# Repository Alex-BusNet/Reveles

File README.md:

**Reveles** (<i>verb</i>) - Latin; to discover or detect.

<ul style="list-style-type: none">
	<li><a href="#about">About</a></li>
	<li><a href="#tools-needed">Tools needed</a></li>
	<li><a href="#setup">Setup</a>
		<ul>
			<li><a href="#installing-linux">Installing Linux</a></li>
			<li><a href="#installing-git">Installing Git</a></li>
			<li><a href="#setting-up-your-working-directories">Setting Up Your Working Directories</a></li>
			<li><a href="#installing-qt-host-pc">Installing Qt</a></li>
			<li><a href="#building-and-configuring-opencv">Building and Configuring OpenCV</a>
				<ul>
					<li><a href="#setup">Setup</a></li>
					<li><a href="#build">Build</a></li>
				</ul>
			</li>
			<li><a href="#installing-wiringpi">Installing WiringPi</a></li>
			<li><a href="#installing-raspicam">Installing Raspicam</a></li>
			<li><a href="#setting-up-the-cross-compiler-tools">Setting Up the Cross Compiler Tools</a></li>
		</ul>
	</li>
	<li><a href="#building-reveles">Building Reveles</a>
		<ul>
			<li><a href="#obtaining-reveles">Obtaining Reveles</a></li>
			<li><a href="#bringing-it-all-together">Bringing it all Together</a></li>
		</ul>
	</li>
	<li><a href="#troubleshooting">Troubleshooting</a>
		<ul>
			<li><a href="#eglfs-not-found">EGLFS not found</a></li>
			<li><a href="#0x300b">Error = 0x300b</a></li>
			<li><a href="#fonts-not-found">Fonts not found</a></li>
			<li><a href="#undefined-reference-glibcxx_3421">Undefined Reference GLIBCXX_3.4.21</a></li>
			<li><a href="#unable-to-deploy-project-to-rpi">Unable to Deploy Project to RPi</a</li>
		</ul>
	</li>
	<li><a href="#updating-the-reveles-repository-with-git">Updating the Reveles Repository with Git</a>
		<ul>
			<li><a href="#tips-on-how-to-avoid-merge-conflicts-with-git">Tips on How to Avoid Merge Conflicts with Git</a></li>
		</ul>
	</li>
	<li><a href="#d-bus">D-Bus</a>
		<ul>
			<li><a href="#making-changes-to-the-xml-d-bus-definition-file">Making Changes to the XML D-Bus Definition File</a>
				<li><a href="#adding-new-signals-and-methods">Adding New Signals and Methods</a></li>
				<li><a href="#d-bus-standard-type-parameters">D-Bus Standard-Type Parameters</a></li>
				<li><a href="#adding-new-signals-and-methods-with-custom-type-objects">Adding New Signals and Methods with Custom-Type Objects</a></li>
			</li>
			<li><a href="#updating-the-interface-and-adaptor">Updating the Interface and Adaptor</a></li>
		</ul>
	</li>
	<li><a href="#credits">Credits</a></li>
</ul>

## About
Reveles is designed to be an autonomous navigation robot. It will be capable of taking a coordinate provided to it and travel to that location using an onboard GPS sensor, in addition to ultrasonic and passive infrared (PIR) sensors. 

This project contains one Qt .pro project file for RevelesCore and the GUI. Additionally there are Arduino .ino and Python .py files that are used for device communication and motor control.

This walkthrough will assume that the end user is starting from a clean slate (no linux install) and has little experience using linux.

> From herein, folders will be denoted in **bold** while filenames will be denoted in _italics_.

You can skip to [Bringing it all Together](#bringing-it-all-together "Bringing it all Together") if you have Reveles already set up on a linux system and built.<br>
Required space (Host machine): 10 GB (During setup and build. This can be reduced later.)

## Tools needed 
> NOTE: We will download each of these when appropriate in the walkthrough. This is just a list of what we will be installing.

+ Any linux distro (I did this successfully on Ubuntu 16.04 LTS)
+ [Latest version of QtCreator](https://www.qt.io/download-qt-for-application-development "Qt Latest download")
+ WiringPi
+ Raspicam
+ Reveles project (obviously)
+ CMake
+ Git
+ A Raspberry Pi running Raspbian Stretch

## Setup
### Installing Linux
There are two ways to run linux 1) Virtual Machine (VM) or 2) Dual Boot. This guide will walk through a VM install.

1. Download Oracle Virtual Box [here](https://www.virtualbox.org/wiki/Downloads "Oracle VirtualBox").
2. Download a Linux distribution of your choice. I used [Ubuntu 16.04 LTS](https://www.ubuntu.com/download/desktop "Ubuntu Desktop").
> NOTE: Save the .iso file to a location you can get to easily. We will need this later.
> NOTE: Ubuntu is a pretty widely used Linux distro and is pretty friendly for beginners.

3. Once both are downloaded, install Oracle Virtual Box and then run it once the installation completes.
4. Select "New" from the toolbar and give the machine a name. Set the type as 'Linux' and set the version to Ubuntu.
> NOTE: The bit type will depend on what you downloaded. The default should be 64-bit.

5. Set how much memory you want the VM to use. This uses the memory built in to your computer so be sure to leave some for your regular OS to run. 2-3 GB should be plenty for Ubuntu.
6. You will need to create a new virtual disk for the VM to run. Give it a name and allocate at least 20 GB to the system. If you don't know what you are doing, you can leave the other settings at their defaults.

At this point you should now be back on the VirtualBox Manager screen. Select your newly created VM and scroll down the info screen to the 'Storage' window.

7. Find the Controller: IDE setting and click on "[Optical Drive] Empty".
8. Navigate to where you saved the linux distro and select it.

You are now ready to load the VM.
9. Click the 'Start' arrow in the toolbar and follow the on screen steps to installing the distro.
> NOTE: During the install, the OS may throw a warning about wiping the hard drive and formatting it. Don't worry about this; The VM acts only within the virtual disk you created in step 6. This will NOT modify any hard drive on your computer.

Once the install completes, the VM will restart. You may be prompted to remove the installation media before restarting. VitrualBox should automatically remove the .iso file. Simply press 'Enter' to continue with the reboot.
<hr>

> The rest of this guide will be working within the Linux VM we just made, and on the Raspberry Pi

### Installing Git
1. Open a terminal window and check to see if Git is already installed by entering the following into the terminal: `git`
> NOTE: Where the terminal is varies by distro. On Ubuntu it can be found by opening the search and typing 'terminal' into the text field. Some Debian based distros have the terminal accessible in the taskbar by default. You may want to lock the terminal to the taskbar for later use (right-click icon and select 'Lock to Launcher').

2. If git was not found enter the following command:
	`$ sudo apt-get install git`

3. (OPTIONAL) You can configure git for easier use with the following commands:<br>
	`$ git config --global user.email "you@example.com"`<br>
	`$ git config --global user.name "Your name"`
	
### Setting Up Your Working Directories
**OPTIONAL** Since there are a lot of parts to this project, it is recommended that you make a dedicated folder for this on your host machine. 

1. **[Host PC]** In your linux distro, you should set up a folder similar to this:
```
/ # root directory
|-home
  |-USER_NAME # the name of the account you are developing Reveles in
    |-CrossDevelopment # Here we will store everything we need for Reveles.
      |-Qt # We will install Qt creator here.
```
> NOTE: We will place other folders inside the `CrossDevelopment` directory later.

2. **[RPi]** You may also choose to create a folder to store some needed files for the Pi.
```
\ # root directory
|-home
  |-pi
    |-Reveles
      |-build # We will place the Reveles executables here
```
> NOTE: We will place additional folders in `Reveles` later.

### Installing Qt (Host PC)
All linux distros have a built-in package manager (aptitude on Debian/Ubuntu) which does include a Qt package. However this will install Qt version 5.3.2 which may not compile Reveles correctly.
Reveles requires Qt version 5.9 or newer. The latest version can be acquired [here](https://www.qt.io/download-qt-for-application-development "Qt Latest download"). 

1. **[Host PC]** The download from Qt's web site will download a .run file. To make this file run as an executable,<br>	right-click -> Properties -> Permissions -> 'Allow executing file as program'.

2. **[Host PC]** Run the installation file the same as you would on Windows.

> NOTE (1): Set the install location to the `~/CrossDevelopment/Qt` folder we made earlier.
> NOTE (2): This is simply to give us the Qt creator. We will configure the IDE later for compiling to the Pi with the proper tools.

### Building And Configuring OpenCV
#### Setup
Revles' object detection system uses the OpenCV framework. These steps will guide you through setting up OpenCV on the RPi and cross compile environment

1. **[RPi]** First we need to set up our directory to work in.<br>
```ShellSession
$ cd
$ mkdir opencv opencv/sources opencv/build opencv/contrib opencv/python
```

2. **[RPi]** Download OpenCV and OpenCV contrib modules<br>
```ShellSession
$ cd opencv/sources
$ wget https://github.com/opencv/opencv/3.4.0.zip
$ unzip 3.4.0.zip
$ cd ../contrib
$ wget https://github.com/opencv/opencv-contrib/master.zip
$ unzip master.zip
```
> At this point, our folder structure should looks like so:
> ```
> ~/Reveles/opencv
>  	    |->build
>  	    |->contrib
>  	    |  |->opencv_contrib-master
>  	    |     |->doc
>  	    |     |->modules
>  	    |     |->samples
>  	    |->python
>  	    |->sources
>     	       |->3.4.0
>        	  |->3rdparty
>        	  |->apps
>        	  |->cmake
>        	  |->CMakeFiles
>        	  |->data
>        	  |->doc
>        	  |->include
>        	  |->modules
>        	  |->platforms
>        	  |->samples
> ```

3. **[RPi]** (optional) We can make the paths easier to work with by copying the subfolders in **contrib** and **sources** up one level. You should end up with something like so:
> ```
> ~/Reveles/opencv
>  	    |->build
>  	    |->contrib
>  	    |  |->doc
>  	    |  |->modules
>  	    |  |->samples
>  	    |->python
>  	    |->sources
>     	       |->3rdparty
>     	       |->apps
>     	       |->cmake
>     	       |->CMakeFiles
>     	       |->data
>     	       |->doc
>     	       |->include
>     	       |->modules
>     	       |->platforms
>     	       |->samples
> ```

4. **[RPi]** Before we can build OpenCV, we need to make sure we have the proper dependencies.
```ShellSession
$ cd ~/Reveles/opencv/build
$ sudo apt-get install cmake build-essential pkg-config
$ sudo apt-get install libjpeg-dev libtiff5-dev libjasper-dev libpng12-dev
$ sudo apt-get install libavcodec-dev libavformat-dev libswscal-dev libv4l-dev
$ sudo apt-get install libxvidcore-dev libx264-dev
$ sudo apt-get install libgtk2.0-dev libgtk-3-dev
$ sudo apt-get install libatlas-base-dev gfortran
$ cd ../python
$ wget https://bootstrap.pypa.io/get-pip.py
$ sudo python get-pip.py
$ sudo python3 get-pip.py
$ pip install numpy
$ cd ../build
```
> NOTE (1): While Reveles does not use Python for it's image processing, it is a good idea to install numpy because OpenCV will look for it during configuration.<br>
> NOTE (2): `python` will run the script for python 2.7, and `python3` will run the script for python 3.6 (or what ever verion of python 3 is installed). I recommend doing both since OpenCV will configure itself for both Python 2 and Python 3.

If you are using Raspbian Stretch, then the native GCC version is 6.3 (as of 1/30/2018). In order to get OpenCV to work with our cross development environment, we need GCC 4.8.

5. **[RPi]** Check the current version of GCC with `$ gcc -v`.<br>
There should be a line similar to this at the bottom of the output: `gcc version 4.8.5 (Raspbian 4.8.5-4)`<br>
> NOTE: Your output will most likely show GCC version 6. My RPi already has been adjusted to use 4.8, which is the output shown above.

If your GCC is not 4.8, we need to get it and set it as the default.
```ShellSession
$ sudo apt-get install -t stretch gcc-4.8* cpp-4.8* g++-4.8* c++-4.8* -y
$ sudo update-alternatives --config gcc
$ sudo update-alternatives --config g++
$ sudo update-alternatives --install /usr/bin/gcc gcc /usr/bin/gcc-4.8 10
$ sudo update-alternatives --install /usr/bin/g++ g++ /usr/bin/g++-4.8 20
$ sudo update-alternatives --install /usr/bin/cc cc /usr/bin/gcc 30
$ sudo update-alternatives --set cc /usr/bin/gcc
$ sudo update-alternatives --install /usr/bin/c++ c++ /usr/bin/g++ 30
$ sudo update-alternatives --set c++ /usr/bin/g++
$ sudo update-alternatives --config gcc
$ sudo update-alternatives --config g++
```

Once again, check your GCC version with `gcc -v`. You should now see the same output as above.

#### Build
We should now be ready to build OpenCV.

1. **[RPi]** Make sure we are in the **build** directory (`~/Reveles/opencv/build`). You can check this with `$ pwd`. 

2. **[RPi]** First we need to configure OpenCV with CMake. There are a few variables we need to pass to CMake in order to get proper configuration. If you setup the directory the same as this tutorial, then you can copy the command exactly as writen. If you did not, match the folder structure, or you are using a user other than "pi", then make sure you change the directories to match your system.
```ShellSession
$ cmake -D CMAKE_BUILD_TYPE=Release -D CMAKE_INSTALL_PREFIX=/usr/local \
-D OPENCV_EXTRA_MODULES_PATH=/home/pi/opencv/contrib/modules \
-D INSTALL_PYTHON_EXAMPLES=OFF \
-D INSTALL_C_EXAMPLES=OFF \
-D BUILD_EXAMPLES=OFF \
-D _GLIBCXX_USE_CXX11_ABI=0 \
-D CMAKE_C_COMPILER=/usr/bin/gcc \
-D CMAKE_CXX_COMPILER=/usr/bin/g++ \
../sources
```
> NOTE (1): The _GLIBCXX_USE_CXX11_ABI flag is for some compatibility fixes. Newer versions of GCC work with the newer standards of C++ (C++14 for GCC 6+) which has brought changes to how some functions are defined in the C++ Standard Library (found in libstdc++11.so on Linux systems). Since we are using GCC 4.8, this flag may be unneeded, but I have included it anyways.<br>

> NOTE (2): The CMAKE_C_COMPILER and CMAKE_CXX_COMPILER flags are also unneeded if you followed all the steps when installing and configuring GCC 4.8, but once again I choose to include it anyway to make sure CMake grabbed to correct GCC version (since GCC 6 is still installed). You could also set the paths to `/usr/bin/gcc-4.8` and `/usr/bin/g++4.8` respectively if you want to be super cautious.<br>

> NOTE (3): If you wish to play with OpenCV in your free time, you can set the `INSTALL_C_EXAMPLES`, `INSTALL_PYTHON_EXAMPLES` and `BUILD_EXAMPLES` flags to `ON`, I have them off to save space.<br>

> NOTE (4): If your are running your Pi in CLI mode, then you may wish to save the CMake output to file so you can review it before building. Simply append `|& tee <filename>` to the CMake command. 

3. **[RPi]** Let CMake run, it will take a couple of minutes. Once it finishes, check the output to make sure everything was found. The output should look like this [file](https://github.com/Alex-BusNet/Reveles/CMake_Config_output.txt) if done correctly (it's long so I'm not going to put it in the README).

4. **[RPi]** Once the output is correct we need to configure the swap file before compiling. By default, the RPi allocates 100 MB by default. This is not enough to compile OpenCV and it will freeze near the end if you forget to change the swap size.
```ShellSession
$ sudo nano /etc/dphys-swapfile

// Comment out the line that says CONF_SWAPSIZE=100 and add CONF_SWAPSIZE=1024 to a line beneath it
// CTRL+X to exit nano. Press Y if it asks to save changes.

$ sudo /etc/init.d/dphys-swapfile stop
$ sudo /etc/init.d/dphys-swapfile start
```

5. **[RPi]** Now we can build OpenCV. Use the command `make -j4` to start building OpenCV. This can take about an hour, be sure to keep an eye on the RPi's temp. If you don't have a fan attached to your Pi, find a fan to blow air over it (or blow on it a couple of times when the thermometer appears; it worked for me)

6. **[RPi]** Once it has completed successfully, install OpenCV with `sudo make install`.

7. **[RPi]** After installing it, run `sudo ldconfig` to make sure all the libraries are linked properly.

8. **[RPi]** **RESET THE SIZE OF YOUR SWAP FILE!** It is highly recommended that you DO NOT leave the swap file at 1024MB. Follow step 4 above to set your swap file back to 100MB.

9. **[RPi]** (Optional) We can check OpenCV works by executing a simple python script:<br>
`$ python`
```python
>>> import cv2
>>> cv2.__version__
>>> exit
```
You should get `3.4.0` as the output.

### Installing WiringPi
In order to access the GPIO from C++, we need to download and build the WiringPi project.

2. **[RPi]** Clone the wiringPi repository to the `Reveles` folder we made earlier.
```ShellSession
$ cd ~/Reveles
$ git clone git://git.drogon.net/wiringPi
```
3. **[RPi]** Build the wiringPi library:
```ShellSession
$ cd wiringPi
$ ./build
```
> The `./build` command will automatically install the libraries and header files into your `/usr/local/` directory.

### Installing Raspicam
If you choose to use the Raspberry Pi Camera module with Reveles, then you will also need to download and build the Raspicam library.

1. **[RPi]** Before we can build Raspicam, we need to install a few dependencies:
```ShellSession
$ sudo apt-get install cmake build-essential pkg-config
```

2. **[RPI]** Clone the Raspicam library to the `Reveles` directory.
```ShellSession
$ cd ~/Reveles
$ git clone https://github.com/cedricve/raspicam
$ cd raspicam
$ mkdir build
$ cd build
$ cmake ..
```

> NOTE: Make sure CMake found the OpenCV libraries. If CMake found the libraries, you should see `CREATE OPENCV_MODULE=1` in the output.

3 **[RPi]** If everything is good with CMake, then you can go ahead and install Raspicam.
```ShellSession
$ make
$ sudo make install
$ sudo ldconfig
```

### Setting Up the Cross Compiler Tools

1.**[RPi]** Before we get started, there are a few settings that need to be configured. Open up the raspberry pi configuration and set the following:
```
Boot to	   = CLI
GPU Memory = 256 MB
SSH	   = enable
```
>Note: You may get a warning saying that the password for user 'pi' has not been changed. You can change this if you wish but it is not critical for this project.

Reboot when prompted to do so.

2.**[RPi]**  If you are running Raspbian Stretch, then you will also need to update the RPi:  
```ShellSession
$ sudo rpi-update
$ reboot
```

3.**[RPi]** Now we need to configure some dependencies for Qt.<br>
  1. Open the sources list with `sudo nano /etc/apt/sources.list` and uncomment the deb-src line (this should be about the third line of the file).<br>
  2. Save the file (CTRL+X -> y -> ENTER).<br>
  3. Update the system and get some additional libraries.
		```ShellSession
		$ sudo apt-get update		
		$ sudo apt-get build-dep qt4-x11		
		$ sudo apt-get build-dep libqt5gui5		
		$ sudo apt-get install libudev-dev libinput-dev libts-dev libxcb-xinerama0-dev libxcb-xinerama0
		```
		
4.**[RPi]** Prepare the target directory
```ShellSession
$ sudo mkdir /usr/local/qt5pi
$ sudo chown pi:pi /usr/local/qt5pi
```

5.**[Host PC]** Create the working directory
```ShellSession
$ mkdir ~/CrossDevelopment/raspi
$ cd ~/CrossDevelopment/raspi
$ git clone https://github.com/raspberrypi/tools`
```

6.**[Host PC]** Create a sysroot. This folder contains a copy of files on the pi that we need for compilation.
```ShellSession
$ mkdir sysroot sysroot/usr sysroot/opt sysroot/usr/local
$ rsync -avz pi@<IP address of RPi>:/lib sysroot
$ rsync -avz pi@<IP address of RPi>:/usr/include sysroot/usr
$ rsync -avz pi@<IP address of RPi>:/usr/lib sysroot/usr
$ rsync -avz pi@<IP address of RPi>:/opt/vc sysroot/opt
$ rsync -avz pi@<IP address of RPi>:/usr/local/include sysroot/usr/local
$ rsync -avz pi@<IP address of RPi>:/usr/local/lib sysroot/usr/local
```

7.**[Host PC]** Adjust symlinks by running the following script:
```ShellSession
$ wget https://raw.githubusercontent.com/riscv/riscv-poky/master/scripts/sysroot-relativelinks.py
$ chmod +x sysroot-relativelinks.py
$ ./sysroot-relativelinks.py sysroot
```

Now we are ready to set up Qt for Raspberry Pi<br>
8.**[Host PC]** Get the qtbase and configure Qt with the following:
```ShellSession
$ git clone git://code.qt.io/qt/qtbase.git -b 5.9.4
$ cd qtbase
$ ./configure -release -opengl es2 -device linux-rasp-pi3-g++ \
-device-option CROSS_COMPILE=/home/USER_NAME/CrossDevelopment/raspi/tools/arm-bcm2708/gcc-linaro-arm-linux-gnueabihf-raspbian-x64/bin/arm-linux-gnueabihf- \
-sysroot /home/USER_NAME/CrossDevelopment/raspi/sysroot \
-opensource \
-confirm-license \
-make libs \
-prefix /usr/local/qt5pi \
-extprefix /home/USER_NAME/CrossDevelopment/raspi/qt5pi \
-hostprefix /home/USER_NAME/CrossDevelopment/raspi/qt5
$ make -jN
$ make install
```
> NOTE (1):  N is the number of parallel jobs to run (assume 1 per core) You can use this to speed up the build time. e.g. A computer with a quad-core processor would use the command `make -j3`
> 
> NOTE (2): If you fail at any point, you can reset qtbase with `git clean -dfx` while in the qtbase folder.

9.**[Host PC]** Once `make install` completes, deploy Qt to the Pi:
```ShellSession
$ cd ~/CrossDevelopment/raspi
$ rsync -avz qt5pi pi@r<IP address of Pi>:/usr/local
```

10.**[Host PC]** We can test that everything works by building and running an example. First, build an example:
```ShellSession
$ cd ~/CrossDevelopment/raspi/qtbase/examples/opengl/qopenglwidget
$ ~/CrossDevelopment/raspi/qt5/bin/qmake
$ make
$ scp qopenglwidget pi@<IP address of Pi>:/home/pi
```

11.**[RPi]** Before we can run the example, we need to configure a few things on the Pi.
```ShellSession
$ echo /usr/local/qt5pu/lib | sudo tee /etc/ld.so.conf/d/00-qt5pi.conf
$ sudo ldconfig
```

12.**[RPi]** We now need to fix some of the EGL/GLES libraries for the Pi.
```ShellSession
$ sudo mv /usr/lib/arm-linux-gnueabihf/libEGL.so.1.0.0 /usr/lib/arm-linux-gnueabihf/libEGL.so.1.0.0_backup
$ sudo mv /usr/lib/arm-linux-gnueabihf/libGLESv2.so.2.0.0 /usr/lib/arm-linux-gnueabihf/libGLESv2.so.2.0.0_backup
$ sudo ln -s /opt/vc/lib/libEGL.so /usr/lib/arm-linux-gnueabihf/libEGL.so.1.0.0
$ sudo ln -s /opt/vc/lib/libGLESv2.so /usr/lib/arm-linux-gnueabihf/libGLES.so.2.0.0
$ sudo ln -s /opt/vc/lib/libEGL.so /opt/vc/lib/libEGL.so.1
$ sudo ln -s /opt/vc/lib/libGLESv2.so /opt/vc/lib/libGLESv2.so.2
```

13.**[RPI]** We should now be able to run the example we built before.
```ShellSession
$ cd ~/CrossDevelopment/raspi/qtbase/examples/opengl/qopenglwidget
$ ./qopenglwidget
```

>NOTE: If the example does not run, see [Troubleshooting](#troubleshooting) for more help

<hr>

## Building Reveles
### Obtaining Reveles
1. For obtaining Reveles, clone the repository to your VM.
```
$ cd ~/CrossDevelopment
$ git clone https://github.com/Alex-BusNet/Reveles.git
```

Now just open _Reveles.pro_ in QtCreator.

### Bringing it all Together
1. Open _Reveles.pro_ in QtCreator and click on the "Projects" icon on the left.

2. Click on "Manage Kits"

3. Select "Qt Versions" from the tabs across the top of the window.

4. Chances are, Qt did not find the version we just built. So we will have to add it manually. Click on "Add" and then navigate to `~/CrossDevelopment/raspi/qt5/bin/`.

5. Click on _qmake_ and press "Open".

6. Next, go to the "Compilers" tab and click "Add" -> "GCC" -> "C++". Name this compiler Something easy to find like "G++-ARM".

7. Navigate to `~/CrossDevelopment/raspi/tools/arm-bcm2708/gcc-linaro-arm-linux-gnueabihf-raspbian-x64/bin/`

8. Select _arm-linux-gnueabihf-g++_ and press "Open"

9. Check the ABI says arm-linux-generic-elf-32bit. If it says <custom> then click the drop down and select the correct ABI.

10. Go to the "Debuggers" tab and add a new debugger. Name this something like "RPi-Debugger".

11. Go the same folder as the compiler. Select _arm-linux-gnueabihf-gdb_ and press "Open".

12. Click on "Devices" from the options menu and add a new "Generic Linux Device"

13. Give the device a name and configure the IP, username, and password for the device.
>NOTE: The remote device will need SSH enabled on the RPi, and the user being used access the pi will need ownership of the target folder for deploying the application.

14. Once the device is configured, Qt will test the connection. If the test fails, check your IP, username, password, as well as permissions on the RPi. 
>If you are using the user "pi" and are getting an "access denied" check that "pi" is not listed as "Do not allow" in the SSH config.
>Access the SSH config with `sudo nano /etc/ssh/sshd_config`.

15. Go back to "Build & Run" and select the "Kits" tab. Add a new kit and configure it like so:
```
Name		 		= Raspberry Pi
File system name 		= (leave blank)
Device type	 		= Generic Linux Device
Device		 		= (Select the Raspberry Pi device we made earlier)
Sysroot				= (browse to ~/raspi/sysroot)
Compiler	 		= C: <No Compiler> C++: <G++-ARM>
Environment	 		= (Do not change)
Debugger	 		= RPi-Debugger
Qt version	 		= (Select the version we manually added)
Qt mkspec	 		= (Leave blank)
CMake Tool	 		= (Leave blank)
CMake generator  		= (Do not change)
Additional Qbs Profile Settings = (Do not change)
```

16. Press "Apply" then "OK" the confirm all your changes.

17. On the "Projects" screen, select the Raspberry Pi Kit and select the "Run" option. Check that the "Local File Path" field is not blank.

To make sure everything gets deployed, we need to add two custom steps to the deploy process.

18. Under the "Deployment" section of the "Run Settings", add two "Custom Process Step" options.

19. The first custom step should be configured like so:<br>
```
Command		  = scp
Arguments	  = -r /PATH/TO/REVELES/GUI/Assets pi@<IP address of pi>:/home/pi/Desktop/Reveles
Working directory = %{buildDir}
```

20. The second custom step should be configured like so:<br>
```
Command		  = scp
Arguments	  = -r /PATH/TO/REVELES/RPi/Data pi@<IP address of pi>:/home/pi/Desktop/Reveles
Working directory = %{buildDir}
```

21. Ensure that the RPi is running and then build and run Reveles.

## Troubleshooting
#### EGLFS not found.
__Error message:__ The application failed to start because it could not find or load the Qt platform plugin "eglfs" in ""<br>
__Solution:__<br>
	`$ export QT_QPA_PLATFORM_PLUGIN_PATH=/usr/local/qt5/plugins/platforms`<br>
	`$ export QT_QPA_PLATFORM=eglfs`

#### 0x300b
__Error message:__ Error: could not draw egl surface: Error = 0x300b<br>
__Solution:__<br>
Check first that the system is trying to use `eglfs_brcm` for EGL device integration:<br>
	`$ export QT_LOGGING_RULES=qt.qpa.*=true`<br>
	`$ ./qopenglwidget`<br>
Your output should look something like: 
```
	qt.qpa.egldeviceintegration: EGL device integration plugin keys: ("eglfs_brcm", "eglfs_kms")
	qt.qpa.egldeviceintegration: EGL device integration plugin keys (sorted): ("eglfs_brcm", "eglfs_kms")
	qt.qpa.egldeviceintegration: Trying to load device EGL integration "eglfs_brcm"
	qt.qpa.egldeviceintegration: Using EGL device integration "eglfs_brcm"
	Unable to query physical screen size, defaulting to 100 dpi.
	To override, set QT_QPA_EGLFS_PHYSICAL_WIDTH and QT_QPA_EGLFS_PHYSICAL_HEIGHT (in millimeters).
	qt.qpa.input: libinput: input device 'Logitech Optical USB Mouse', /dev/input/event0 is a pointer caps = relative-motion button
	qt.qpa.input: libinput: input device 'Apple Inc. Apple Keyboard', /dev/input/event1 is a keyboard
	qt.qpa.input: libinput: input device 'Apple Inc. Apple Keyboard', /dev/input/event2 is a keyboard
	qt.qpa.input: libinput: input device 'Raspberry Pi Sense HAT Joystick', /dev/input/event3 is a keyboard
```
If the system is not using `eglfs_brcm` then try rerunning step 11 in [Setting Up the Cross Compile Tools](#setting-up-the-cross-compile-tools). If the error persists, you may need to start over.

#### Fonts not found
__Error message:__ QFontDatabase: Could not find font directory <directory>/lib/fonts.<br>
__Solution:__<br>
```ShellSession
$ sudo mkdir -p <directory>/lib/fonts>
$ sudo cp /usr/share/fonts/truetype/dejavu/* <directory>/lib/fonts>
```

#### Undefined Reference GLIBCXX_3.4.21
__Error message:__ `undefined reference to 'std::__cxx11::basic_string<char, std::char_traits<char>, std::allocator<char> >::_M_create(unsigned int&, unsigned int)@GLIBCXX_3.4.21'*`
> *Exact function may differ

__Solution:__<br>
This error means one of a few things:<br>
1) The version of GCC used to compile OpenCV on the RPi and the version of GCC used to compile Reveles on the Host machine are not the same.<br>
2) Your libstdc++.so the host machine is using is not the same as the one used by the RPi when compiling OpenCV.<br>
This solution addresses the second option:
**[Host PC]**
```ShellSession
$ cd ~/CrossDevelopment/raspi/tools/arm-bcm2708/gcc-linaro-arm-linux-gnueabihf-raspbian-x64/arm-linux-gnueabihf/lib
$ ls -l | grep libstdc++.so
```
> One of the files that are returned should be a symbolic link: `libstdc++.so.6 -> libstdc++.so.6.0.19` (The .0.19 is the version that comes with the cross compile tools). Make note of the numbers listed after the .so.6 in the file name.

**[RPi]**: Now we need to find the `libstdc++.so` file on the pi
```ShellSession
$ cd /usr/lib/arm-linux-gnueabihf
$ ls -l | grep libstdc++.so
```
> Once again, we should see a file that is listed as symbolic link pointing to another file. On the original RPi for Reveles this looks like: `libstdc++.so.6 -> libstdc++.so.6.0.22`. Notice how the last number on the file is different from the one on our host machine. We need this version on our host to elimanate the error.

**[Host PC]**
We can fix the linked files like so:
```ShellSession
$ cd ~/CrossDevelopment/raspi/tools/arm-bcm2708/gcc-linaro-arm-linux-gnueabihf-raspbian-x64/arm-linux-gnueabihf/lib
$ mv libstdc++.so.6 libstdc++.so.6.bak
$ mv libstdc++.so libstdc++.so.bak
$ scp pi@<IP address of RPi>:/usr/lib/arm-linux-gnueabihf/libstdc++.so.6.0.22 ./
$ ln -s libstdc++.so.6.0.22 libstdc++.so.6
$ ln -s libstdc++.so.6.0.22 libstdc++.so
```
Reveles should now be able to compile.

#### Unable to Deploy Project to RPi
There isn't really an error message with this one, you should see a red bar in the bottom right corner of the screen (the same place that shows when a build is successful or not).<br>
__Solution:__<br>
First, you need to find the IP address of the RPi. Second, there are 3 places that need to be changed:<br>
	1. Click "Projects" on the left toolbar, then select "Run" under the Raspberry Pi Kit.
	2. Under the two "Custom Process Step" options, change the IP address to the IP address of the Pi.
	3. Go to "Devices" (Manage Kits -> Devices) and change the IP address of the Raspberry Pi device.
	4. Open up a new terminal window and enter the following:<br>
		`ssh pi@<IP address of pi>`
> Once you are ssh-ed into the RPi, you can exit out of the ssh session with `exit`, and then close the window.
	5. Re-deploy Reveles to the RPi.

## Updating the Reveles Repository with Git
The following command assume you are in the top level folder of where the repository is located on your hard drive. (For me this is /home/USER_NAME/Reveles/Reveles)

+ Adding files to staging area: <br>
  + Add all unstaged files: `$ git add .`<br>
  + Add specific file: `$ git add <filename>`<br>
  + Add entire directory: `$ git add <directory name>` <br>

+ To create a commit use:
	`$ git commit [-a] [-m <message>]`
> NOTE (1): The `-a` flag tells Git to commit everything this is both staged and unstaged. Omit the `-a` flag to commit only staged files. 
> NOTE (2): If `-m` is omitted, or no message is given, Git will prompt you to enter a commit message. If a commit does not have a message with it, it will NOT be pushed to the repository.

+ Push the commit to the repo use:
	`$ git push origin master`

+ If you wish to see what files are staged or affected by the current commit, use: `$ git status`.

+ To get the latest updates from the repo to your local working version use: `$ git pull origin master`
> NOTE: There is another command call `fetch` which will check if there are updates, but will not change the files in your working version.

### Tips on How to Avoid Merge Conflicts with Git
1. Before you push new changes to the repository, run the `fetch` command to check if any updates have been made since you last pulled from the repo.

2. If changes have been made since you last pulled, you can save your changes using the `stash` command.
> `Stash` will save a 'snapshot' of your local working version and store it in a different location. This will revert your working version to match the last commit you pulled.
  1. To save your changes use: `$ git stash -u`
  2. Update your local version.
  3. (OPTIONAL) To see a list of all your stored stashes, use: `$ git stash list`
> NOTE: stash@{0} is always your most recently created stash.
  4. Reapply your changes by using `$ git stash pop`.
> NOTE (1): Most of the time, you will only need to pass 0 as N in this command.

> NOTE (2): This method is not fool-proof. There can still be merge conflicts if the changes on the repo override code you changed in your working version. At this point, you will have to go through the conflicted files manually and delete the code that should be changed.

> HINT: In each conflicted file, the sections that could not be merged will look like this:
>```
>/*
> * Unaffected code.
> */
><<<<<<< HEAD
>/* 
> * Conflicted code 
> * from repository
> */
>=======
>/* 
> * Conflicted code 
> * from your changes
> */
>>>>>>> <branch name>
>/*
> * Unaffected code.
> */
>```
> From here, simply modify the code as needed by deleting the HEAD or local section, or join the two together. Once you have fixed a conflict, besure to remove the `<<<<<<< HEAD`, `=======`, and `>>>>>>> <branch name>` markers from the file before commiting files.
  5. Once all all the files are conflict free (and correct), you can push your newest changes to the repo.

## D-Bus
The Core and GUI programs communicate along the D-Bus on the service named "com.reveles.core" and through the object "/Core". The definition for the D-Bus interface and adapter is outlined in _revelesdbus.xml_ in the GUI and RPi subprojects. These two files MUST BE THE SAME in order for the two programs to communicate properly. You may also add the signals directly to the _reveles\_dbus\_adaptor.h_ and _reveles\_dbus\_interface.h_ in both the GUI and CORE folders. The CORE and GUI each need an D-Bus Adaptor and D-Bus Interface to communicate in two directions.

### Making Changes to the XML D-Bus Definition file
#### Adding New Signals and Methods
A signal is formatted like so in the _.xml_ file:

```xml
<!-- Signal with no parameters -->
<signal name="<signal name>" />

<!-- Signal with standard-type parameters -->
<signal name="<signal name>">
	<arg name="<arg name>" type="<variable type>" direction="[in|out]">	
</signal>

<!-- Signal with custom-type parameters -->
<signal name="<signal name>">
	<annotation name="org.qtproject.QtDBus.QtTypeName.[In0|Out0]" value="<custom type name>" />
	<arg name="<arg name>" type="<variable type>" direction="[in|out]">	
</signal>
```

>NOTE (1): Methods are formatted the same as signals, except the word `signal` is replaced with `method`<br>
>NOTE (2): When adding an annotation for custom-type parameters, using `.Out0` will result in the first `arg` configured as `out` being used as the return type.<br>
>NOTE (3): To give a signal a parameter, declare the argument as `out`. If an annotation node is included in the definition of the signal, be sure to use `.In0` in the annotation name. When we run _qdbusxml2cpp_ we will get a warning about using `In0` and declaring the `arg` as `out`, just ignore these. If you fix them to make _qdbusxml2cpp_ happy, your signals will not be genereated correctly.

#### D-Bus Standard-Type Parameters:
The [D-Bus Specification](https://dbus.freedesktop.org/doc/dbus-specification.html) outlines the ASCii characters that can be used in the `type` field of the `arg` node. The specification is pretty long and contains a lot of lower-level information that most of us aren't too concerned with. So here's a table of all the type codes:

| D-Bus type | ASCII code | Qt type  |
|:----------:|:----------:|:--------:|
|BYTE        |y           |uchar     |
|BOOLEAN     |b           |bool      |
|INT16       |n           |short     |
|UINT16	     |q           |ushort    |
|INT32       |i           |int       |
|UINT32      |u           |uint      |
|INT64       |x           |qlonglong |
|UINT64      |t           |qulonglong|
|DOUBLE      |d           |double    |
|STRING      |s           |QString   |
|OBJECT\_PATH|o           |QDBusObject\_Path |
|SIGNATURE   |g           |QDBusSignature   |
|VARIANT     |v           |QDBusVariant     |
|Struct      |(\<type(s)\>)|          |
|Array	     |a\<type\>   |          |
|Dictionary  |{\<type(s)\>}|          |

>NOTE: Don't worry too much about OBJECT\_PATH and SIGNATURE types. We will hardly see them in this project.

#### Adding New Signals and Methods with Custom Type Objects
The Qt D-Bus module supports custom types but some additional code is needed.<br>
Say for example we have the following struct:

```c++
struct MyStruct {
	int foo;
	string bar;
};
```

In order to use `MyStruct` on the D-Bus, we have to tell Qt that it is a type that can be sent along the bus. To do this we add the following line:<br>
`Q_DECLARE_METATYPE(MyStruct)`. <br>
We will also need to add `#include <QMetaType>` to to our source file.<br>
If we are using a `struct`, we need to also tell Qt how to marshall and demarshall the datatype. We can do this by adding:

```c++
QDBusArgument &operator<<(QDBusArgument &argument, const MyStruct& ms)
{
    argument.beginStructure();
    argument << ms.foo;
    argument << ms.bar;
    argument.endStructure();
    return argument;
}

const QDBusArgument &operator>>(const QDBusArgument &argument, MyStruct &ms)
{
    argument.beginStructure();
    argument >> ms.foo;
    argument >> ms.bar;
    argument.endStructure();
    return argument;
}
```

Our source file should now look like so:

```c++
#include <QMetaType>
#include <QtDBus/QDBusArgument>
#include <cstring>

struct MyStruct {
	int foo;
	string bar;
};

Q_DECLARE_METATYPE(MyStruct)

QDBusArgument &operator<<(QDBusArgument &argument, const MyStruct& ms)
{
    argument.beginStructure();
    argument << ms.foo;
    argument << ms.bar;
    argument.endStructure();
    return argument;
}

const QDBusArgument &operator>>(const QDBusArgument &argument, MyStruct &ms)
{
    argument.beginStructure();
    argument >> ms.foo;
    argument >> ms.bar;
    argument.endStructure();
    return argument;
}
```

<br>
In our _.xml_ file we would then use our `MyStruct` object like so:

```xml
<signal name="mySignal">
	<annotation name="org.qtproject.QtDBus.QtTypeName.In0" value="MyStruct" />
	<arg name="ms" type="(xs)" direction="out">	
</signal>
```

### Updating the Interface and Adaptor
If changes are made to _revelesdbus.xml_ the following commands will generate the corresponding _.cpp_ and _.h_ files. The commands will NOT update any other source file, so make sure any changes to the slots or signals are properly reflected in _revelesgui.cpp_ and _revelescore.cpp_<br>

```ShellSession
$ export PATH=/path/to/Qt/%VERSION%/gcc_64/bin:$PATH	
$ cd /path/to/reveles/RPi
$ qdbusxml2cpp -i Common/datatypes.h -c RevelesDBusAdaptor \
-a reveles_dbus_adaptor.h:reveles_dbus_adaptor.cpp revelesdbus.xml
$ cd ../GUI
$ qdbusxml2cpp -c RevelesDBusInterface -p reveles_dbus_interface.h:reveles_dbus_interface.cpp \
-i ../RPi/Common/datatypes.h revelesdbus.xml
```

## Credits
Code base for Trine University ECE Senior Design Project 2017-18.<br>
Created by Frank Hittel, Alisha Johnson, and Alex Portolese.<br>
All rights reserved. &copy; 2017

Walkthrough written against the following resources:
* [RaspberryPi2EGLFS](https://wiki.qt.io/RaspberryPi2EGLFS)
* [Using Custom Types with D-Bus](https://techbase.kde.org/Development/Tutorials/D-Bus/CustomTypes)
* [Raspbian Stretch: Install OpoenCV 3 + Python on your Raspberry Pi](https://www.pyimagesearch/com/2017/09/04/raspbian-stretch-install-opencv-3-python-on-your-raspberry-pi)
* [GCC 4.8 on Raspberry Pi Wheezy](https://somewideopenspace.wordpress.com/2014/02/28/gcc-4-8-on-raspberry-pi)

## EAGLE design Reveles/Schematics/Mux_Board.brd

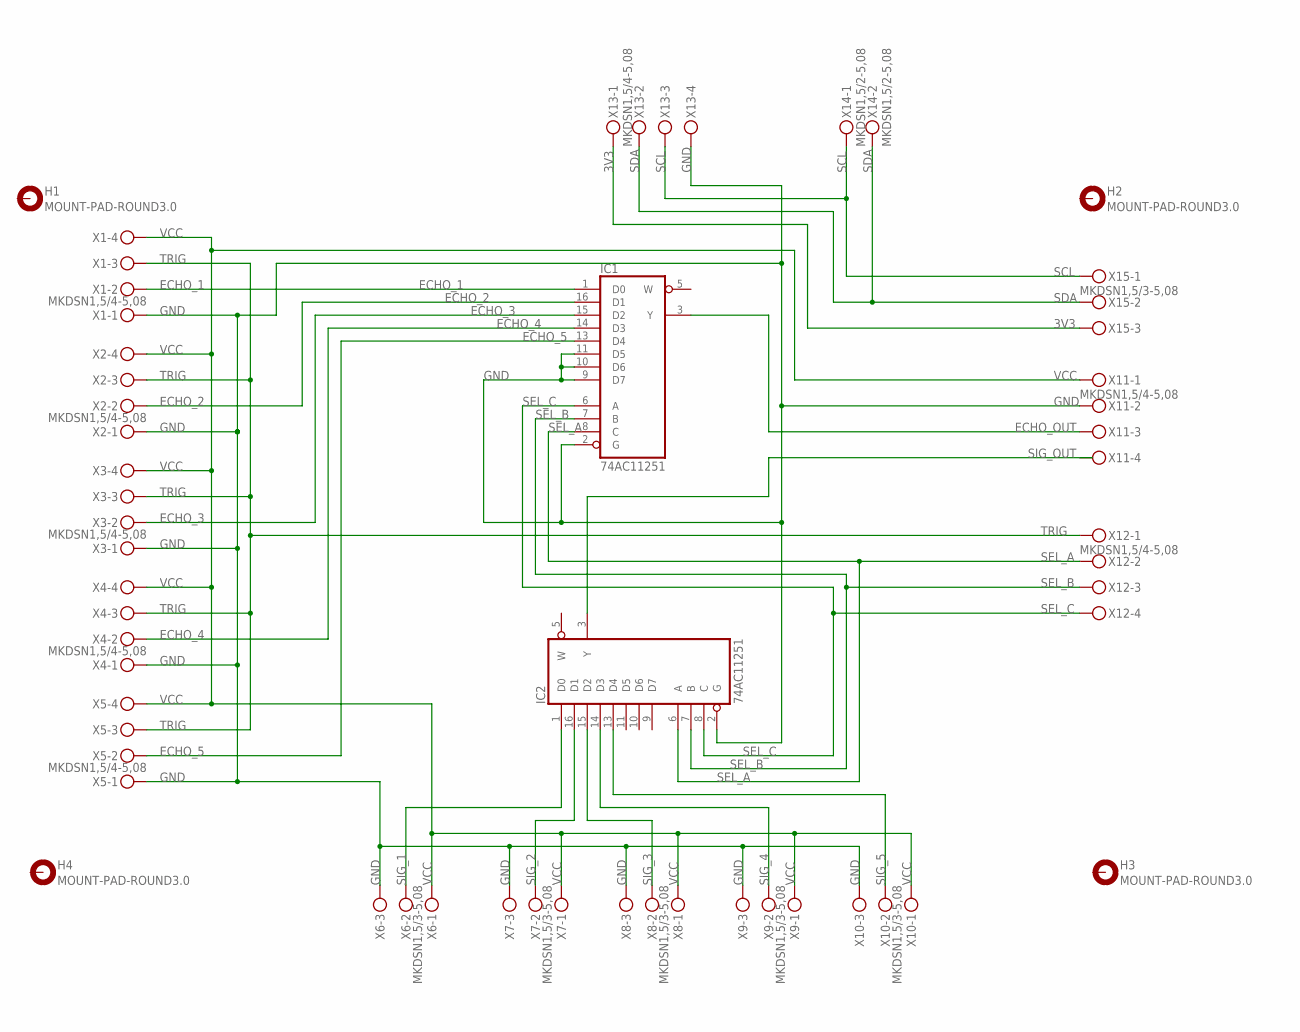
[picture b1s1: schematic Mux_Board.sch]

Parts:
H1, H2, H3, H4: MOUNT-PAD-ROUND3.0; 3,0-PAD
IC1, IC2: 74AC11251; DIL16
X1, X2, X3, X4, X5, X11, X12, X13: MKDSN1,5/4-5,08
X6, X7, X8, X9, X10, X15: MKDSN1,5/3-5,08
X14: MKDSN1,5/2-5,08

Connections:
3V3: X13.1, X15.3
ECHO_1: IC1.1 (D0), X1.2
ECHO_2: IC1.16 (D1), X2.2
ECHO_3: IC1.15 (D2), X3.2
ECHO_4: IC1.14 (D3), X4.2
ECHO_5: IC1.13 (D4), X5.2
ECHO_OUT: IC1.3 (Y), X11.3
GND: IC1.2 (G), IC1.4 (GND), IC1.9 (D7), IC1.10 (D6), IC1.11 (D5), IC2.2 (G), IC2.4 (GND), X1.1, X2.1, X3.1, X4.1, X5.1, X6.3, X7.3, X8.3, X9.3, X10.3, X11.2, X13.4
SCL: X13.3, X14.1, X15.1
SDA: X13.2, X14.2, X15.2
SEL_A: IC1.8 (C), IC2.6 (A), X12.2
SEL_B: IC1.7 (B), IC2.7 (B), X12.3
SEL_C: IC1.6 (A), IC2.8 (C), X12.4
SIG_1: IC2.1 (D0), X6.2
SIG_2: IC2.16 (D1), X7.2
SIG_3: IC2.15 (D2), X8.2
SIG_4: IC2.14 (D3), X9.2
SIG_5: IC2.13 (D4), X10.2
SIG_OUT: IC2.3 (Y)
TRIG: X1.3, X2.3, X3.3, X4.3, X5.3, X12.1
VCC: IC1.12 (VCC), IC2.12 (VCC), X1.4, X2.4, X3.4, X4.4, X5.4, X6.1, X7.1, X8.1, X9.1, X10.1, X11.1

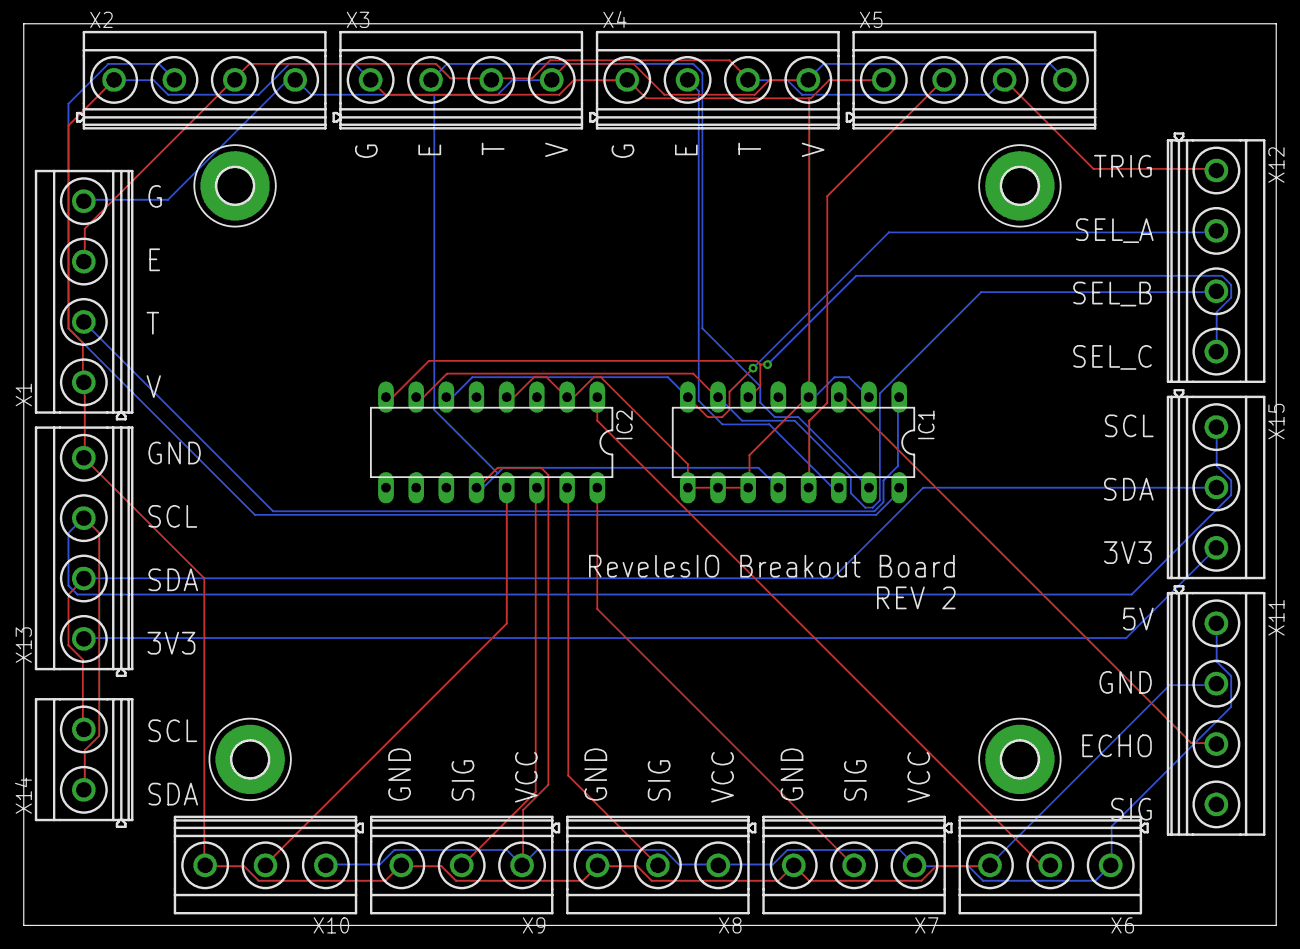
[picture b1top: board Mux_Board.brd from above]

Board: 2 copper layers, 105.4 x 75.9 mm, 21 parts (0 on the bottom side), 20 nets.

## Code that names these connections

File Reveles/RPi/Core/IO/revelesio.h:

#ifndef REVELESIO_H
#define REVELESIO_H

#include <QObject>
#include <stdint.h>
#include <chrono>
#include "RPi/Common/datatypes.h"
#include "Libraries/wiringPi/wiringPi.h"
#include "Libraries/wiringPi/wiringPiI2C.h"

//---------------------------
//     Sensor GPIO pins
//(use wiringPi's numbering)
#define SEL_A    0 // GPIO-17
#define SEL_B    2 // GPIO-27
#define SEL_C    3 // GPIO-22
#define  ECHO   12 // GPIO-10
#define   SIG   13 // GPIO-9
#define  TRIG    7 // GPIO-4
//---------------------------

#define TIMEOUT 500000

//-----------------------
//  I2C Device Addresses
#define  XG_ADDR  0x6B
#define MAG_ADDR  0x1E
#define  ARDUINO  0x04
//-----------------------

class RevelesIO : public QObject
{
    Q_OBJECT
public:
    RevelesIO();

    static RevelesIO *instance();
    void initIO();
    void SendMotorUpdate(int motorSpeedFactor);
    GPSCoord ReadGPS();
    int readSensor(SensorType type);
    void triggerUltrasonic(uint8_t sel);

    long durat;
    float dist, inch;
    bool isrWait;
    std::chrono::steady_clock::time_point begin, end;
private:

signals:
    void echoReady(float dist, QString unit);
};

#endif // REVELESIO_H

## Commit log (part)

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2017-11-28 Initial code commit. Contains skeleton for GPS sensor and map objects.
2017-11-28 Added placeholder for arduino files.
2017-11-28 Added Readme file
2017-11-28 Added license (GNU General Public License) and .gitignore for Qt-based projects.
2017-11-29 Working on building a python module to act as an interface between the GPIO and the main program. RevelesIO was a test project that is most likely going to be deleted. Reveles is the main project and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
2017-11-30 Add files via upload
    A separate DC motor control program stubbed with a potentiometer and button to replace the sensors. Enables the motor to spin clockwise and counter-clockwise with varying speeds.
2017-11-30 Fixed local repo so that pybind11 shows up on GitHub
2017-11-30 Updating codebase across devices. The pybind11 library didn't get pushed originally, so I had to push it and then catch all devices up to speed.
2017-11-30 Repo updates.
2017-12-10 Added Project for GUI. This is currently a mockup for our presentation.
2017-12-11 Create Integrated Demo File
    An integrated tech demo file. Consists of the motor file and the sensor file for ease of use.
2017-12-11 Update Integrated Demo File
2017-12-11 This file now has i2c instead of SPI
    I also cleaned up the unused code
2017-12-11 GUI is now more functional for a presentation (hopefully).
2017-12-11 Corrected potential file type error with Integrated_Demo_File in the Arduino code. (File was missing .ino file extension)
2017-12-11 Added Images to menu buttons
2017-12-11 Added I2C communication python script
2017-12-11 Updated DesignNotes.txt with some points of interest discussed in our presentation.
2017-12-23 Updating repo with work I have been doing. Not much overall has changed, I am currently working on getting the code to compile for the RPi (Since the RPi runs linux, the code has to be built in Qt on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
2017-12-24 Updated project to be a bit better organized (in terms of what Qt sees) and also got the project to build successfully (yay!).
2017-12-24 Added instructions for building and deploying Reveles on Linux
2017-12-27 Updated README
    Formatting tweaks and link fixes
2017-12-27 More formatting changes to README
    I always have issues with this.
2017-12-27 Updated README
    Hopefully for the last time. Added Table of Contents
2017-12-28 Updated README (again) with up-to-date instructions for successfully building .AppImage files for RevelesCore. Also add the newest .AppImage file into the 'Reveles_Release_Builds' folder.
2018-01-04 Updated README (again)
    In an drawn out, agonizing attempt to get Qt to build and run properly on a raspberry pi, all the previous instructions for building and running Reveles are no longer valid.
2018-01-08 Added skeleton class for on-screen keyboard.
2018-01-10 GPIO is now working properly for a single HC-SR04 through RevelesIO and displays the distance on the GUI. Also added a sub-project for a virtual keyboard to allow user input while the program is runn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
2018-01-11 Got a virtual keyboard working with the 'Add location' screen. Removed VirtualKeyboard Project
2018-01-12 Updated README
    Minor corrections
2018-01-16 Got D-Bus communication working between the GUI and RevelesCore. Also updated the README with information regarding making changes to the D-Bus .xml file.
2018-01-16 Updated README
    Minor formatting corrections
2018-01-16 Updated README
    Fixed link to D-Bus Specification
2018-01-16 Updated README
    Minor formatting corrections.
2018-01-17 Added class to handle the LSM9DS1 (Accelerometer/Gyro/Magnetometer) on a lower level, i.e. handling the actual calculations of the data that is recieved from the device. Also added a newclass called 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
2018-01-18 Fixed some compilation issues. Also added additional operator overloads to the Vector2i class. Removed the unused GPIO class in the RPi/Common folder.
2018-01-21 Added Markov chain foundation to the AnalyticalEngine class. The MC is being used (for now) as a way to handle person movement prediction. We are going to need our sensors and GPS module working in o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
2018-01-22 Added floating type vectorclasses (cartesian and polar). Also added conversion functions for reading Gaussian values from magnetometer and converting them into degrees. Added code for determining the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
2018-01-24 Add files via upload
    This is the new version. The major emphasis is the integration of sensor data in controlling the speed and direction of the motors. This version is still a heavy WIP.
2018-01-29 Update DC_Motor_Control2.ino
    This is an updated version of the beta motor control program. This program allows to take a ultrasonic reading from the core and decides whether the robot will move forward or backward. Still in the 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
2018-01-30 Added looping function to core in order to cycle through reading the sensors and reporting it to the appropriate places. Also updated the GPIO set up to adjust for the number of sensors planned to be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
2018-01-31 OpenCV FINALLY compiles with Reveles.
2018-02-01 Started to work with the analytical engine using the camera. The HoG algorithm is a bit more intensive than I originally thought and is posing some problems. Need to investigate further while working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
2018-02-04 Got the I2C communication working with the Magnetometer. Need to do some work on the Orient() function in the NavigationAssistant, currently all directions as reading as 'North', 'North-East', or 'Ea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
2018-02-04 Updated NavigationAssistant with proper calculations for reading the magnetometer to determine heading. Added functions to determine bearing between two GPS coordinates and updated the function to ge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
2018-02-05 Updated README
    Reordered a few parts of the guide to follow a more logical path (i.e. installing OpenCV before we sync directories between the RPi and Host PC). Also added a few steps for setting up folder structur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
2018-02-07 Updated the Arduino code for I2C communication with the RPi, meaning I added functionality to parse the command given to the Arduino. I did NOT change any existing functions surrounding motor drive. 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
2018-02-08 Added D-Bus adaptor and interface for CORE -> GUI and GUI -> CORE. This was needed to allow signals to be sent from either application. Also updated some of the I2C control for motor control. Added l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
2018-02-09 Updated the I2C communication format to better handle the data being passed through it. Currently, only communication can be done from RPi to Arduino. The Arduino code (in Reveles_Arduino2.ino) has c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
2018-02-10 Added some rendering to the MapView for the GUI. Also added some log routing to the GUI from the core. Currently the log output for the GUI goes to the 'Log' view in the settings screen, but is not s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
2018-02-13 Fixed compile errors.
    Fixed some errors in the I2C command decoding on the Arduino. Currently the left motor does not seem to be driving, need to figure out why. May be a code issue.
2018-02-15 Updated RevelesIO to properly handle I2C comms to Arduino to relay motor drive information. This has been tested and is working. Need to do some work on getting GPS data to communicate correctly. Ard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
2018-02-15 Updated Arduino code in Reveles_Arduino2.ino to handle motor control when receiving commands from RPi via I2C. This now works and this is the version currently running on the Arduino. GPS is still a 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
2018-02-15 Added servo control via I2C as well as code to test functionality.
2018-02-15 Note to self: Verify Arduino code before uploading to Github.
2018-02-15 Added some code to let the AnalyticalEngine run and start attempting to adjust path when obstacle is detected.
2018-02-15 Commented out servo testing commands in RevelesCore. May have been generating some interference between motor and servo commands.
2018-02-20 Commented out motor testing code in RevelesCore. Added code to Analytical engine for improved motor drive and turning control. Still need to fine tune AnalyticalEngine::ProcessEnv() which requires co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
2018-02-21 Added pathfinding algorithm to NavigationAssistant. Also did some tweaking to RevelesMap to how the data is stored. RevelesIO now has some code in place to handle I2C comms to the two Nucleos, this i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
2018-02-24 Added new header file: 'rpi.h' to hold some commonly used includes in the RPi project. Updated AnalyticalEngine and NavigationAssistant for a little better handling of path progression, path adjustme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
2018-02-26 Added Accel/Gyro/Mag readings to the GUI. Tweaked the AnalyticalEngine, NavigationAssistant, and RevelesIO for better performance. There are still a few points that need to be tested, such as how the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
2018-02-26 Adjustments to I2C data readings. I could've sworn these changes were already pushed to the repo. Also added latitude/longitude output to Serial for debugging.
2018-02-27 Updated AnalyticalEngine
    Added note in ProcessEnv() for how to help determine how figure out if and how to navigate around a person.
2018-02-28 Added pin to RevelesIO for triggering interrupt to Nucleo. (Note: not implemented)
2018-02-28 Adjusted check logic for I2C comms. For some reason the code seems to get stuck on the GPS read.
2018-03-01 Added demo mode. There is a problem when the application closes when in Demo mode; the RevelesCore provess does not close. When attempting to use the normal navigation mode, RevelesCore closes withou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
2018-03-01 Code tweaks for technical demo. Need to figure out what is going on with I2C comms when using the Arduino andLSM9DS1. Also need to send comm info to GUI from CORE for Arduino and Nucleo status. Motor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
2018-03-05 Fixed Arduino Comm check (was using the Arduino's 'onRequest()' function improperly). Also D-Bus signals to transmit status of Arduino, Nucleos, and PIR (only one for now) to the Status screen in the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
2018-03-06 More adjustments to RevelesIO and AnalyticaEngine for handling I2C communications between Arduino and RPi. COM_CHECK now properly is sent between the two. Still need to test ToF sensors.
2018-03-20 Updated Nucleo I2C Address
2018-03-20 Reverted Nucleo I2C address.
2018-03-22 Added 'edit' feature to locations in GUI. Also updated the AnalyticalEngine to actually send ToF requests to the IO. Also added status checks to RevelesIO to look for a response from the Nucleos inst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
2018-03-27 Added statement in GUI Exit command to turn off the 'hasComms' flag. This will allow the GUI to close in the event the CORE gets hung up and is unable to respond with the exit command.
2018-03-27 Changed active Log messages
2018-03-28 Added DBus signals to relay information from the IO to the Status screen in the GUI.
2018-04-02 Added check to AnalyticalEngine to not run ToFParser if the nucleos cannot be found.
2018-04-02 Added ToF sensor library found by Alisha into the IO class.
2018-04-02 Got ToF sensors working with IO via VL53L0X library. Still need to test with all 8 sensors connected and still need to figure out how to set the addresses of each device. May involve a little tweakin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
2018-04-03 Tweaked a bit of the ToF handling in RevelesIO and AnalyticalEngine.
2018-04-03 Added ToF Address initialize function to Arduino and RevelesIO. The VL53L0X sensors all default their I2C address to 0x29, so we need to change them so we can get values individually from them, howev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
2018-04-05 Adjusted ToF Init function to ignore the front and rear center ToFs.
2018-04-07 Adjusted debug output. Still having issues with ToF and US readings not coming in clearly.
2018-04-07 Adjusted code for reading ToF sensors and US sensors along with adjustments to how the data is handled.
2018-04-09 Fixed ToF sensor initialization. All 6 Satellite sensors are now readable. AnalyticalEngine doesn't appear to be responding properly to the sensor readings, or response is slow. Need to investigate t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
2018-04-09 Updated some arduino code to work with the recent changes to ToF sensor control.
2018-04-09 Tweaks for AnalyticalEngine sensor processing.
2018-04-12 Simplified AnalyticalEngine's logic for robot control.
2018-04-12 More Tweaks to AnalyticalEngine
    Attempting to get Reveles to handle head-on collision avoidance.
2018-04-12 Updated Version
2018-04-21 Formatting changes to README
    Making it more image friendly
2018-04-23 Tweaked servo control.
2018-04-27 Adjustments for Expo
